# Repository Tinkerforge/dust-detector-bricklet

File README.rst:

Dust Detector Bricklet
======================

This repository contains the firmware source code and the hardware design
files. The documentation generator configs can be found at
https://github.com/Tinkerforge/generators

Repository Content
------------------

software/:
 * examples/: Examples for all supported languages
 * build/: Compiled files
 * src/: Source code of firmware
 * Makefile: Makefile to build project

hardware/:
 * Contains KiCad project files and additionally schematics as PDF

datasheets/:
 * Contains datasheets for sensors and complex ICs that are used

Hardware
--------

The hardware is designed with the open source EDA Suite KiCad
(http://www.kicad.org). Before you are able to open the files,
you have to install the Tinkerforge kicad-libraries
(https://github.com/Tinkerforge/kicad-libraries). You can either clone
them directly in hardware/ or clone them in a separate folder and
symlink them into hardware/
(ln -s kicad_path/kicad-libraries project_path/hardware). After that you
can open the .pro file in hardware/ with KiCad and from there view and
modify the schematics and the PCB layout.

Software
--------

If you want to do your own Brick/Bricklet firmware development we highly
recommend that you use our build environment setup script and read the
tutorial (https://www.tinkerforge.com/en/doc/Tutorials/Tutorial_Build_Environment/Tutorial.html).

To compile the C code we recommend you to install the newest GNU Arm Embedded
Toolchain (https://launchpad.net/gcc-arm-embedded/+download).
You also need to install bricklib (https://github.com/Tinkerforge/bricklib)
and brickletlib (https://github.com/Tinkerforge/brickletlib).

You can either clone it directly in software/src/ or clone it in a
separate folder and symlink it into software/src/
(ln -s bricklib_path/bricklib project_path/software/src/ and
ln -s brickletlib_path/brickletlib project_path/software/src/).
Finally make sure to have CMake installed
(http://www.cmake.org/cmake/resources/software.html).

After that you can build the firmware by invoking make in software/.
The firmware (.bin) can then be found in software/build/ and uploaded
with brickv (click button "Flashing" on start screen).

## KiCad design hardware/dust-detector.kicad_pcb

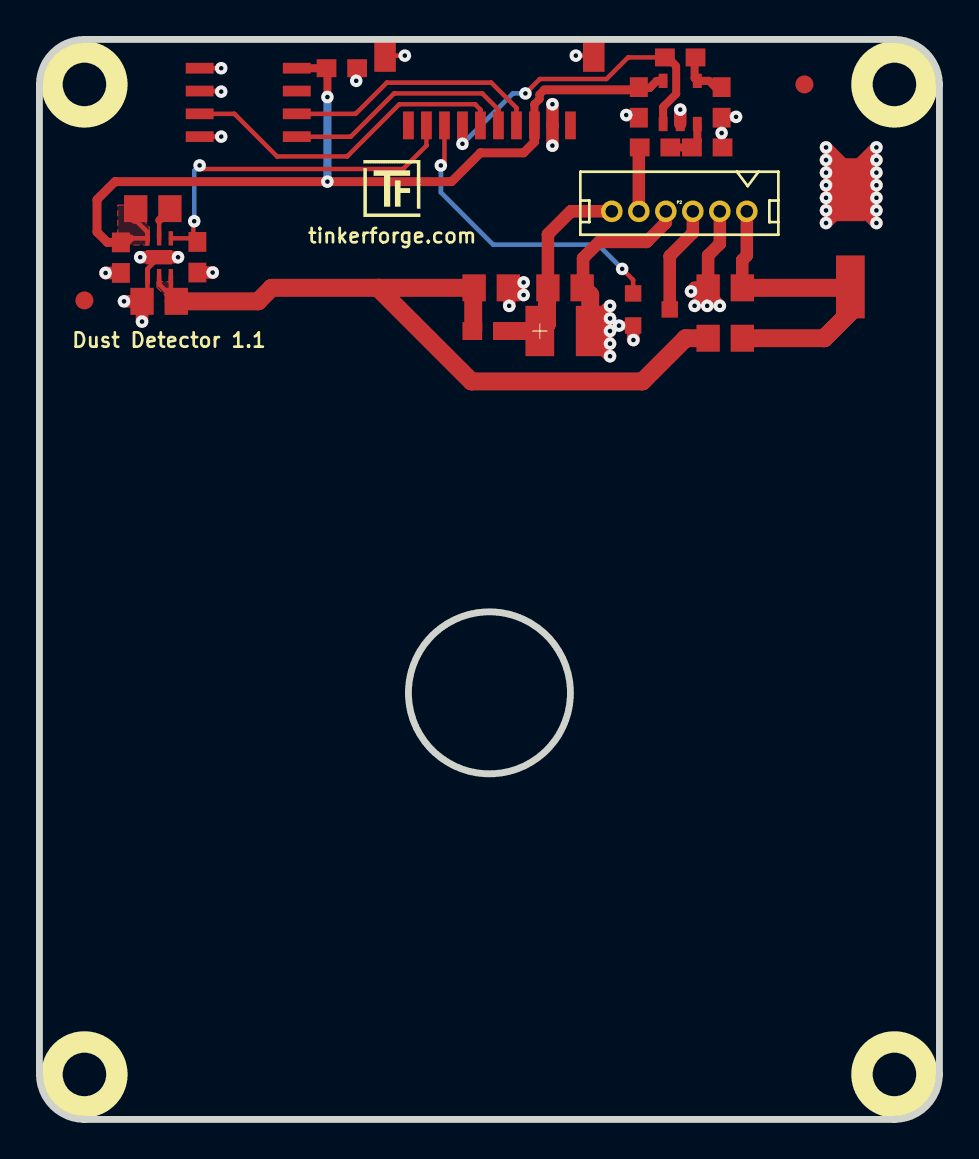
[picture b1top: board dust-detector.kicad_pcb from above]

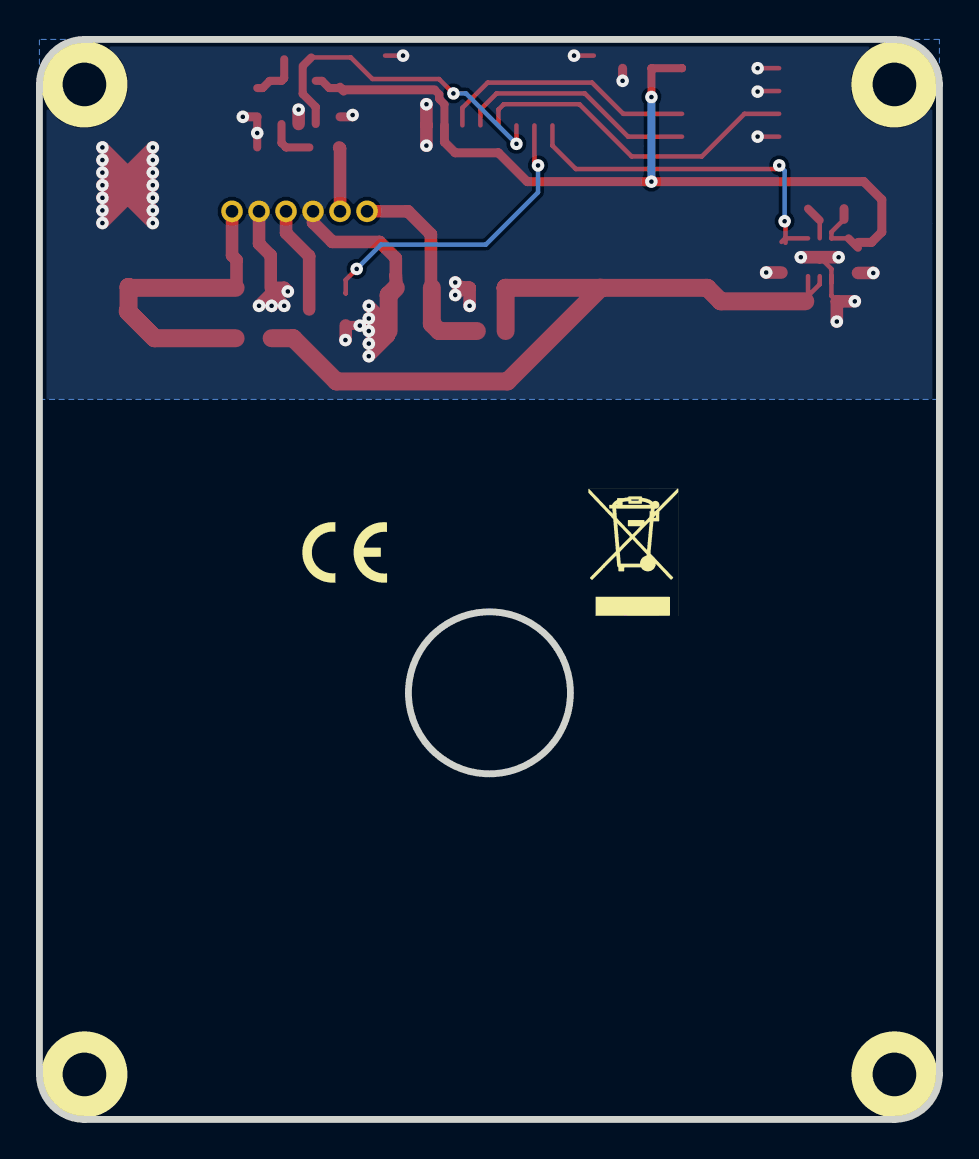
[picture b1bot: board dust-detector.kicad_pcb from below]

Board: 2 copper layers, 50.0 x 60.0 mm, 31 parts (2 on the bottom side), 16 nets.

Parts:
C1: 2.2µF; C0603E
C2, C4: 100nF; C0603E
C3, C5, C6: 4.7µF; C0805E
C7: 100µF; 3528-21
C8: DNP; C0805E
C9: 220µF/35V; ELKO_63
Fiducial_Mark: VAL**; Fiducial_Mark
Fiducial_Mark#2: VAL**; Fiducial_Mark
L1: 1µH; C0805E
L2: INDUCT; C0603E
P1: CON-SENSOR
P2: CONN_6; B6B-ZR
Q1: 2N7002P; SOT23GDS
R1, R2, R3: 10k; R0603E
R4, R5: 12k; R0603E
R6: 150; R0805E
U1: M24C64; SOIC8
U2: FAN4860; UMLP_22
U3: TLV271; SOT23-5
U4, U5, U6, U7: DRILL; DRILL_NP
VAL: CE_5mm
VAL#2: WEEE_7mm_back

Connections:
3V3: C1.1, C2.2, C4.2, L1.1, P1.3, U1.8, U2.6, U3.5
+5V: C3.1, C5.2, L2.2, R6.2, U2.2, U2.3
EN: P1.9, R1.1, U2.4
GND: C1.2, C2.1, C3.2, C4.1, C5.1, C6.1, C7.2, C8.1, C9.2, P1.2, P1.EP, P2.2, P2.4, Q1.S, R1.2, R3.1, R4.1, U1.1, U1.2, U1.4, U2.1, U2.EP, U3.2
unnamed: C6.2, C7.1, L2.1, P2.6
unnamed: C8.2, C9.1, P2.1, R6.1
unnamed: L1.2, U2.5
unnamed: P1.4, U1.6
unnamed: P1.5, U1.5
unnamed: P1.6, U1.3
unnamed: P1.7, R2.2, U3.1
unnamed: P1.8, Q1.G
unnamed: P2.3, Q1.D
unnamed: P2.5, R5.1
unnamed: R2.1, R4.2, U3.4
unnamed: R3.2, R5.2, U3.3

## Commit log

2015-04-23 Add readme
2015-04-23 add hardware files
2015-04-23 change capacitor footprints change pcb size
2015-04-23 Add GP2Y1010AU datasheet
2015-04-23 Add initial version of API implementation
2015-04-30 Add Python examples
2015-05-04 mark capacitor as dnp
2015-05-05 Add Java Examples
2015-05-05 Only apply last_value in bricklet_simple
2015-05-05 Use "dd" for DustDetector variable name
2015-05-05 Add C examples
2015-05-05 Add C# examples
2015-05-05 Add VB.NET examples
2015-05-05 Add Delphi examples
2015-05-05 Add JavaScript examples
2015-05-06 Add Perl examples
2015-05-06 Add PHP examples
2015-06-15 dust-detector-bricklet: Adding MATLAB/Octave examples
2015-06-18 Add Ruby examples
2015-06-18 Add Shell examples
2015-06-18 Add mathematica examples
2015-06-18 Add LabVIEW and Mathematica examples
    Also clean up other examples.
2015-06-19 Remove Python examples from wrong directory
2015-06-24 vbnet: Remove unnecessary parentheses
2015-06-24 delphi: Fix typos
2015-07-23 Make JavaScript browser example textarea readonly
2015-07-27 Cleanup C/C++, C#, Java, Python and Ruby examples
2015-07-29 Reformat changelog
2015-08-03 update schematic
2015-08-07 Use full device class name in Python examples
2015-08-12 Fix minor warnings in C/C++ examples
2015-08-13 Use correct simple value type
2015-08-14 Cleanup Delphi examples
2015-08-18 Cleanup VB.NET examples
2015-08-19 Cleanup Perl examples
2015-08-21 Use shorter print statement in Perl example
2015-09-10 Add .gitignore
2015-09-10 Duplicate cmake call to fix bug during cmake creation
    Also, toolchain is now in bricklib.
2015-09-30 Generator based example cleanup
2015-11-12 matlab: Fix callback handling for R2014a
    http://undocumentedmatlab.com/blog/matlab-callbacks-for-java-events-in-r2014a
2015-11-25 Include date and commit into changelog
2015-11-30 vbnet: Break long line
2016-03-04 dust detector version 1.1 with tht connector
2016-05-18 c: Add missing device destroy call
2016-06-29 Whitespace
2016-07-01 Make the change UID comment more explicit
2017-04-13 csharp: Adapt example
2017-04-21 shell: Adapt example
2017-06-02 octave: Use javaObject instead of deprecated java_new
2017-11-20 Add 3d information (final)
2017-11-20 Add 3d model (*.step & *.FCStd)
2017-11-30 Update examples from generator
2017-12-07 mathematica: Also generate .nb files
2018-01-26 c: Fine-tune printf format
2018-02-02 Update examples
2018-02-19 javascript: Close div tag correctly
2018-02-20 Cleanup KiCad libraries config
    Ensure LibDir=kicad-libraries and LibName1=tinkerforge.
    Remove special library.
2018-05-07 Fix bug in moving average setter
2018-05-24 perl: Use strict in examples
2018-07-11 Add Makefile with docker support
2018-07-11 Remove obsolete generate_makefile scripts
2018-07-11 Update directory structure and build instructions
2018-09-14 vbnet: Fix typo in comment
2018-11-06 Add rust examples
2018-11-07 rust: Accept host names for ip connection, fix naming inconsistencies
2018-11-07 rust: Rename callback receivers.
2018-12-14 Add go examples.
2018-12-18 go: Change import path.
2018-12-18 go: Change import path again.
2018-12-20 rust: Reformat examples.
2019-01-24 mqtt: Add examples.
2019-01-24 mqtt: Fix example header.
2019-01-24 mqtt: Remove executable bit in example permissions.
2019-01-24 go: Minor example fixes.
2019-01-24 mqtt: Minor example fixes.
2019-03-28 mqtt: Fix whitespace.
2019-08-22 c: Adapt to bindings changes
2020-01-13 examples: Use python3 input instead of python2 raw_input.
2020-01-13 examples: mqtt: Remove trailing whitespace.
2020-04-14 mqtt: Fix device name format
2021-10-25 Update KiCad link
    https://www.kicad.org/blog/2021/10/Avoid-links-to-former-kicad-domain/
2022-05-10 go: Fix format string
2022-07-06 Add license files.

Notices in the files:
hardware/dust-detector.kicad_pcb:
Licensed under CERN OHL v.1.1
Copyright (©) 2016, B.Nordmeyer
